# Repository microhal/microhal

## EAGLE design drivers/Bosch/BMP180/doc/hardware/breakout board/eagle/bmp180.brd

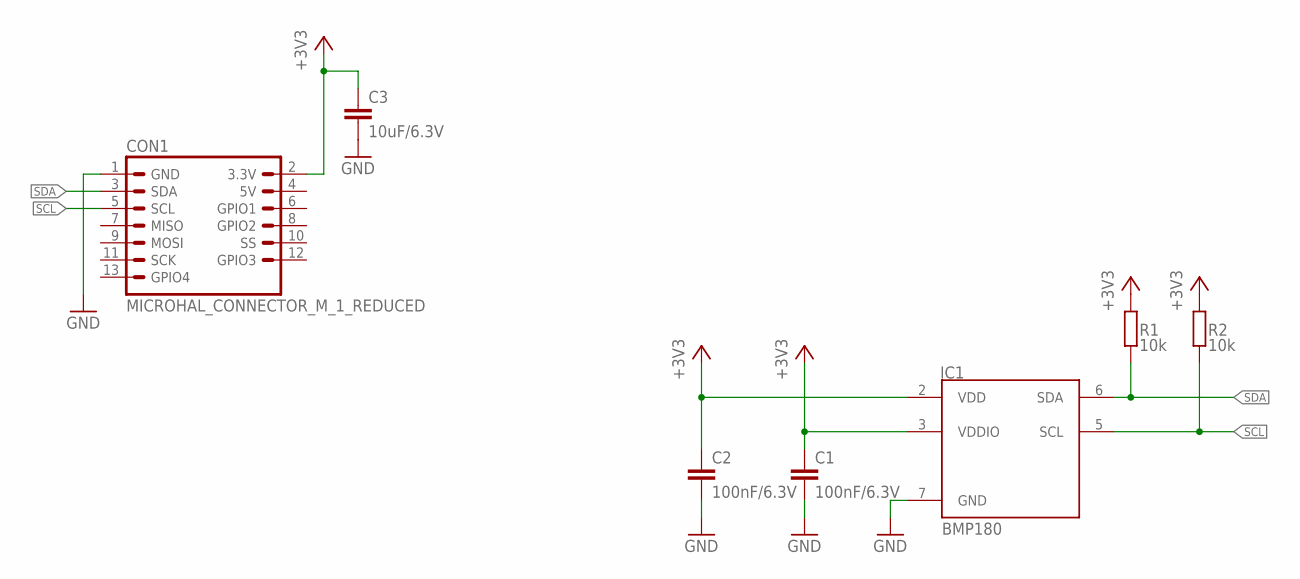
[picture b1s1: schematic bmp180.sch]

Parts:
C1, C2: 100nF/6.3V; C0603K
C3: 10uF/6.3V; C0805K
CON1: MICROHAL_CONNECTOR_M_1_REDUCED; MICROHAL_CONNECTOR_M_1_REDUCED_EDGE
IC1: BMP180; LGA7
R1, R2: 10k; R0603

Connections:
+3V3: C1.1, C2.1, C3.1, CON1.2 (3.3V), IC1.2 (VDD), IC1.3 (VDDIO), R1.2, R2.2
GND: C1.2, C2.2, C3.2, CON1.1 (GND), IC1.7 (GND)
SCL: CON1.5 (SCL), IC1.5 (SCL), R2.1
SDA: CON1.3 (SDA), IC1.6 (SDA), R1.1

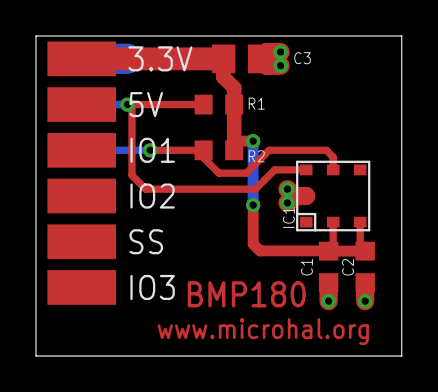
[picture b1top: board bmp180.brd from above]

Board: 2 copper layers, 20.3 x 17.8 mm, 7 parts (0 on the bottom side), 4 nets.

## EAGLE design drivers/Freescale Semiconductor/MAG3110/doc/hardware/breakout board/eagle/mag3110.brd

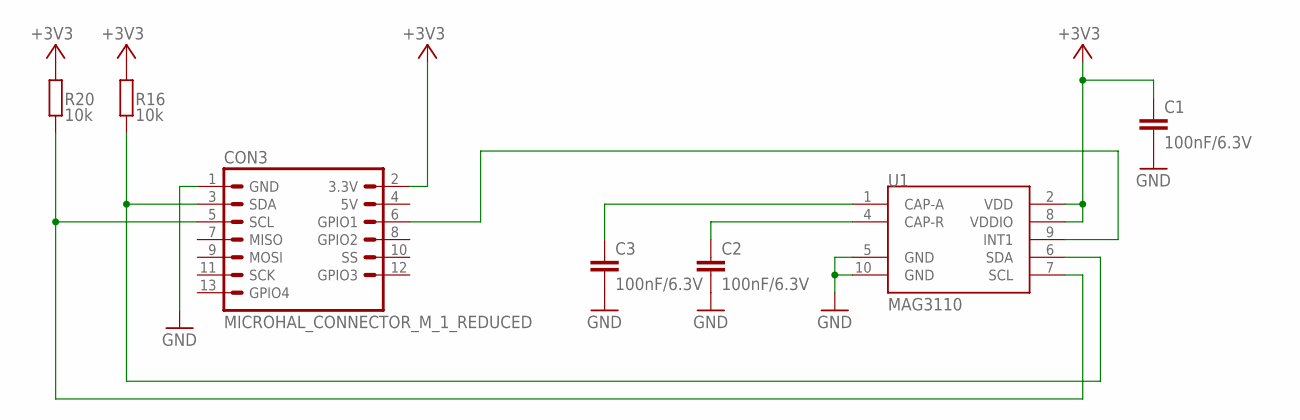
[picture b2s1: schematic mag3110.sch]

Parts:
C1, C2, C3: 100nF/6.3V; C0603K
CON3: MICROHAL_CONNECTOR_M_1_REDUCED; MICROHAL_CONNECTOR_M_1_REDUCED_EDGE
R16, R20: 10k; R0603
U1: MAG3110; DFN-10

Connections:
+3V3: C1.1, CON3.2 (3.3V), R16.2, R20.2, U1.2 (VDD), U1.8 (VDDIO)
GND: C1.2, C2.2, C3.2, CON3.1 (GND), U1.5 (GND), U1.10 (GND)
unnamed: C2.1, U1.4 (CAP-R)
unnamed: CON3.3 (SDA), R16.1, U1.6 (SDA)
unnamed: CON3.5 (SCL), R20.1, U1.7 (SCL)
unnamed: CON3.6 (GPIO1), U1.9 (INT1)
unnamed: C3.1, U1.1 (CAP-A)

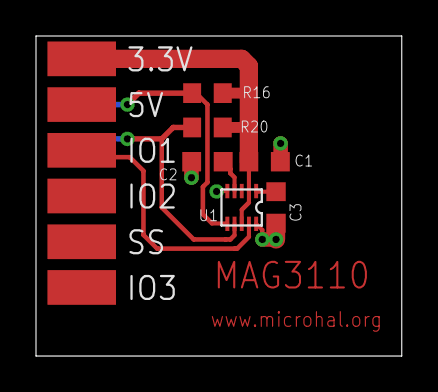
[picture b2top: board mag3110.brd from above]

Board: 2 copper layers, 20.3 x 17.8 mm, 7 parts (0 on the bottom side), 7 nets.

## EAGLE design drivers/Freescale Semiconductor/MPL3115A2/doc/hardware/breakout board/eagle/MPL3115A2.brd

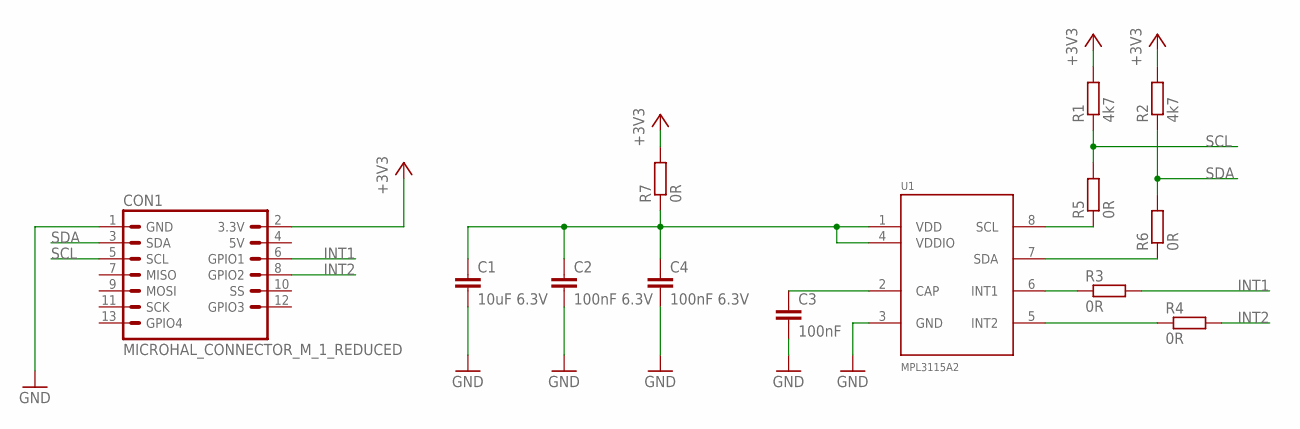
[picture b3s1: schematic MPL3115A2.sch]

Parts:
C1: 10uF 6.3V; C0603K
C2, C4: 100nF 6.3V; C0603K
C3: 100nF; C0603K
CON1: MICROHAL_CONNECTOR_M_1_REDUCED; MICROHAL_CONNECTOR_M_1_REDUCED_EDGE
R1, R2: 4k7; R0603
R3, R4, R5, R6, R7: 0R; R0603
U1: MPL3115A2

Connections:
+3V3: CON1.2 (3.3V), R1.2, R2.2, R7.2
GND: C1.2, C2.2, C3.2, C4.2, CON1.1 (GND), U1.3 (GND)
INT1: CON1.6 (GPIO1), R3.2
INT2: CON1.8 (GPIO2), R4.2
unnamed: R5.1, U1.8 (SCL)
unnamed: R6.1, U1.7 (SDA)
unnamed: C1.1, C2.1, C4.1, R7.1, U1.1 (VDD), U1.4 (VDDIO)
unnamed: C3.1, U1.2 (CAP)
unnamed: R3.1, U1.6 (INT1)
unnamed: R4.1, U1.5 (INT2)
SCL: CON1.5 (SCL), R1.1, R5.2
SDA: CON1.3 (SDA), R2.1, R6.2

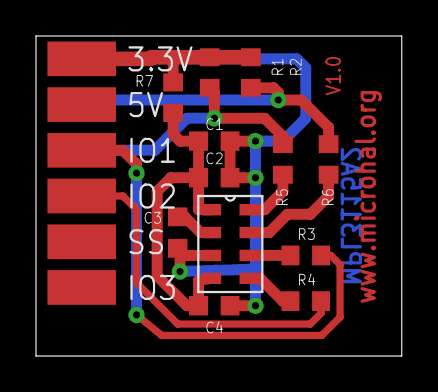
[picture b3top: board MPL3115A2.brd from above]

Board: 2 copper layers, 20.3 x 17.8 mm, 13 parts (0 on the bottom side), 12 nets.

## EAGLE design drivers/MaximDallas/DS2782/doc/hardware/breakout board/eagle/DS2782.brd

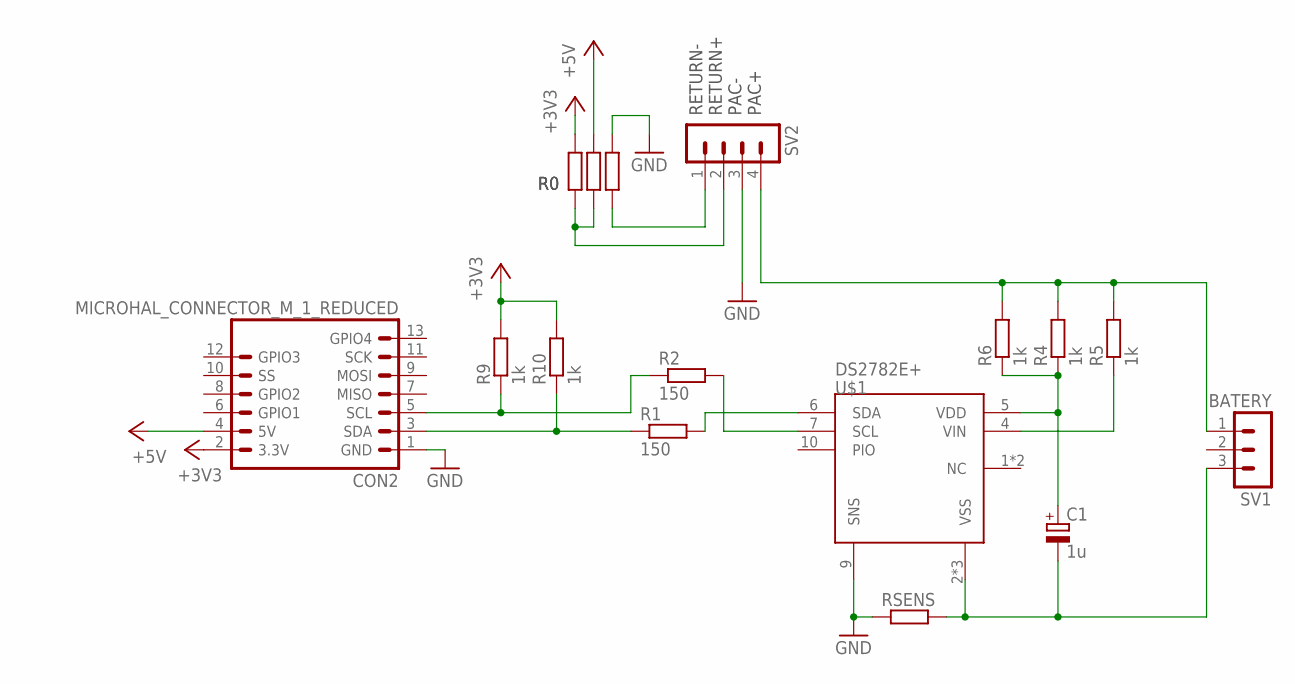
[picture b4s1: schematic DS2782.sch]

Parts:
C1: 1u; 153CLV-0405
CON2: MICROHAL_CONNECTOR_M_1_REDUCED; MICROHAL_CONNECTOR_M_1_REDUCED_EDGE
R1, R2: 150; R0603
R3, R7, R8: R-EU_R0603; R0603
R4, R5, R6, R9, R10: 1k; R0603
RSENS: R-EU_R1206; R1206
SV1: BATERY; MA03-1
SV2: MA04-1
U$1: DS2782E+; TDFN-10

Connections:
+3V3: CON2.2 (3.3V), R8.2, R9.2, R10.2
+5V: CON2.4 (5V), R7.2
GND: CON2.1 (GND), R3.2, RSENS.1, SV2.3, U$1.9 (SNS)
unnamed: R1.2, U$1.6 (SDA)
unnamed: R2.2, U$1.7 (SCL)
unnamed: CON2.3 (SDA), R1.1, R10.1
unnamed: C1.+, R4.1, R6.1, U$1.5 (VDD)
unnamed: R5.1, U$1.4 (VIN)
unnamed: C1.-, RSENS.2, SV1.3, U$1.2 (VSS), U$1.3 (VSS), U$1.PAD1 (VSS)
unnamed: R4.2, R5.2, R6.2, SV1.1, SV2.4
unnamed: R7.1, R8.1, SV2.2
unnamed: CON2.5 (SCL), R2.1, R9.1
unnamed: R3.1, SV2.1

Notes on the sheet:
RETURN- RETURN+ PAC- PAC+

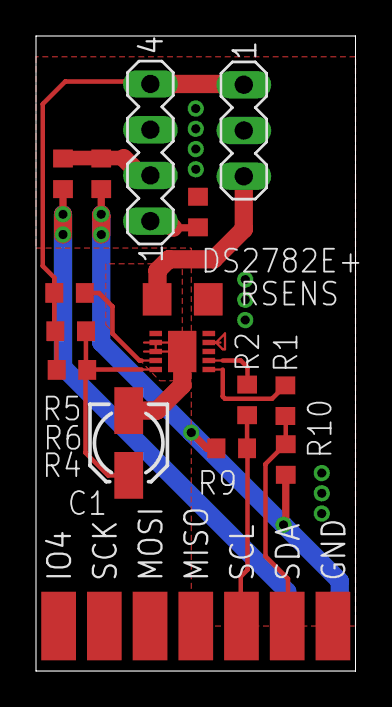
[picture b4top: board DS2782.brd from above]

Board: 2 copper layers, 17.8 x 35.3 mm, 16 parts (1 on the bottom side), 13 nets.

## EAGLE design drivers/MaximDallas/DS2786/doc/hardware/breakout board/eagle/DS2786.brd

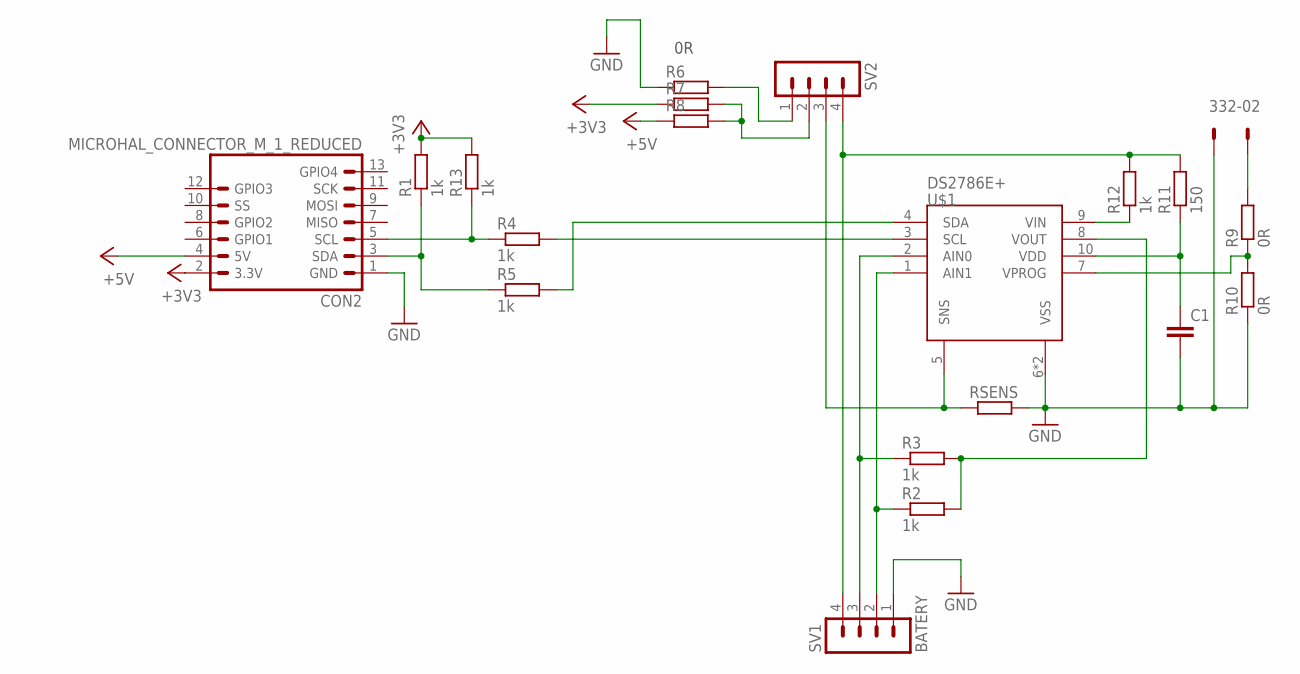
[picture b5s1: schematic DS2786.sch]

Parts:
C1: C-EUC0603; C0603
CON2: MICROHAL_CONNECTOR_M_1_REDUCED; MICROHAL_CONNECTOR_M_1_REDUCED_EDGE
R1, R2, R3, R4, R5, R12, R13: 1k; R0603
R6, R7, R8: R-EU_R0603; R0603
R9, R10: 0R; R0603
R11: 150; R0603
RSENS: R-EU_R1206; R1206
SV1: BATERY; MA04-1
SV2: MA04-1
U$1: DS2786E+; TDFN-10
X1: 332-02

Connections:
+3V3: CON2.2 (3.3V), R1.2, R7.1, R13.2
+5V: CON2.4 (5V), R8.1
GND: C1.2, CON2.1 (GND), R6.1, R10.1, RSENS.2, SV1.1, U$1.6 (VSS), U$1.PAD1 (VSS), X1.1
unnamed: R9.2, X1.2
unnamed: R2.2, R3.2, U$1.8 (VOUT)
unnamed: RSENS.1, SV2.3, U$1.5 (SNS)
unnamed: CON2.5 (SCL), R4.1, R13.1
unnamed: CON2.3 (SDA), R1.1, R5.1
unnamed: R4.2, U$1.3 (SCL)
unnamed: R5.2, U$1.4 (SDA)
unnamed: R11.2, R12.2, SV1.4, SV2.4
unnamed: R6.2, SV2.1
unnamed: R7.2, R8.2, SV2.2
unnamed: C1.1, R11.1, U$1.10 (VDD)
unnamed: R9.1, R10.2, U$1.7 (VPROG)
unnamed: R12.1, U$1.9 (VIN)
unnamed: R2.1, SV1.2, U$1.1 (AIN1)
unnamed: R3.1, SV1.3, U$1.2 (AIN0)

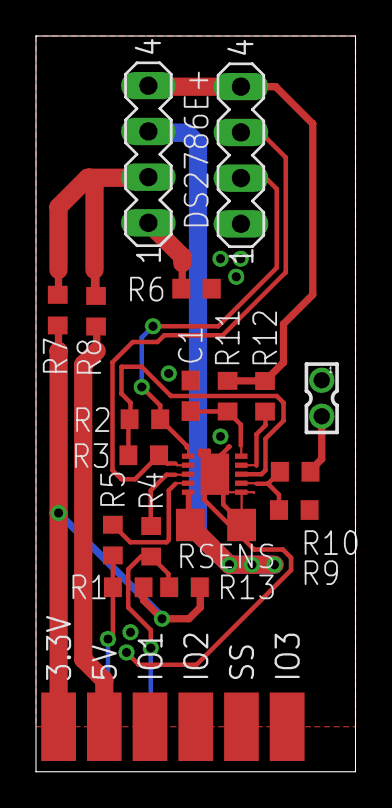
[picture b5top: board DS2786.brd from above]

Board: 2 copper layers, 17.8 x 40.9 mm, 20 parts (0 on the bottom side), 18 nets.

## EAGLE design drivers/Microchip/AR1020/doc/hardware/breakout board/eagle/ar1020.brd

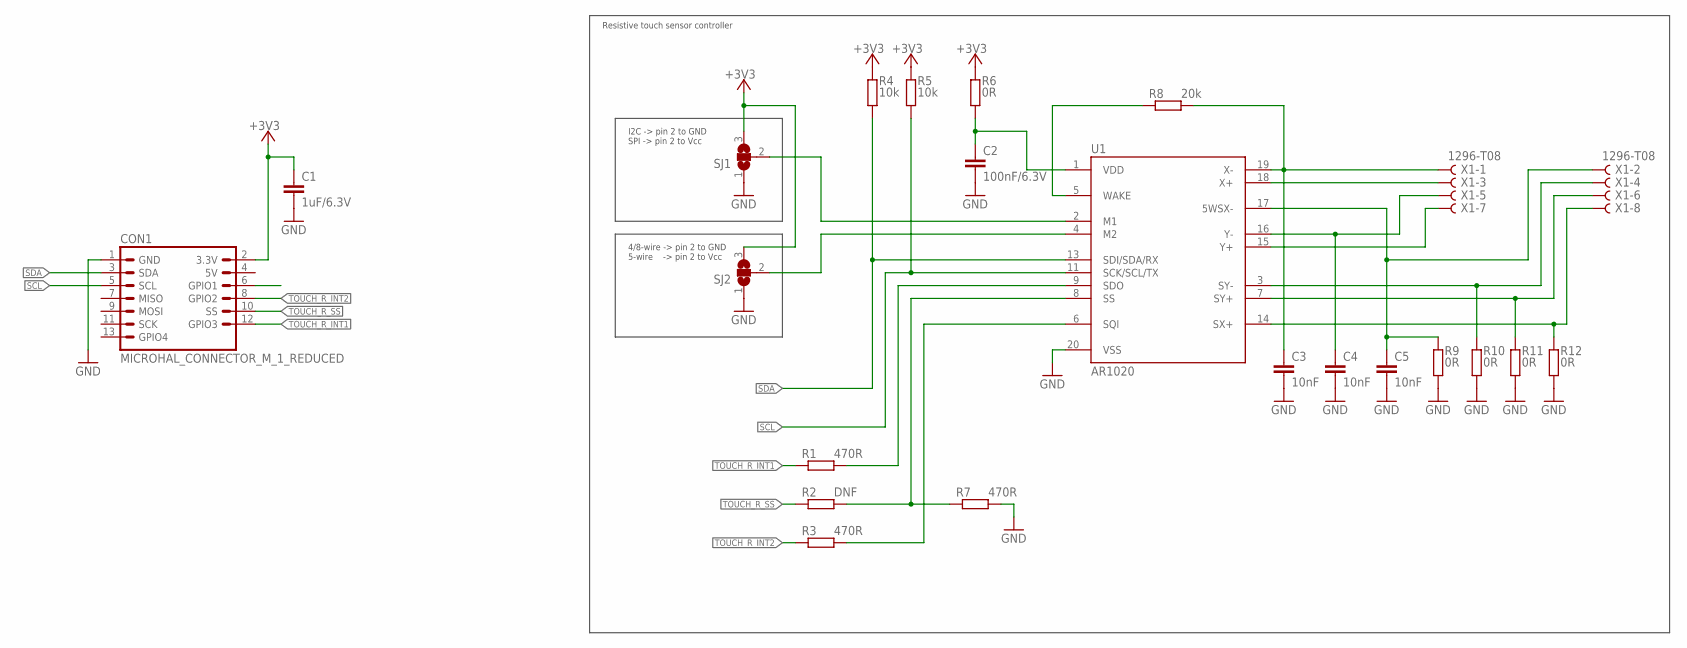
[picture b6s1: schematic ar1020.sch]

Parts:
C1: 1uF/6.3V; C0603K
C2: 100nF/6.3V; C0603K
C3, C4, C5: 10nF; C0603K
CON1: MICROHAL_CONNECTOR_M_1_REDUCED; MICROHAL_CONNECTOR_M_1_REDUCED_EDGE
R1, R3, R7: 470R; R0603
R2: DNF; R0603
R4, R5: 10k; R0603
R6, R9, R10, R11, R12: 0R; R0603
R8: 20k; R0603
SJ1, SJ2: SJ2W; SJ_2
U1: AR1020; SSOP20
X1: 1296-T08; 1296-08

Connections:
+3V3: C1.1, CON1.2 (3.3V), R4.1, R5.1, R6.1, SJ1.3, SJ2.3
GND: C1.2, C2.2, C3.2, C4.2, C5.2, CON1.1 (GND), R7.1, R9.2, R10.2, R11.2, R12.2, SJ1.1, SJ2.1, U1.20 (VSS)
unnamed: SJ1.2, U1.2 (M1)
unnamed: SJ2.2, U1.4 (M2)
unnamed: C2.1, R6.2, U1.1 (VDD)
unnamed: R8.2, U1.5 (WAKE)
unnamed: C3.1, R8.1, U1.19 (X-), X1.1
unnamed: C4.1, U1.16 (Y-), X1.5
unnamed: C5.1, R9.1, U1.17 (5WSX-), X1.2
unnamed: U1.18 (X+), X1.3
unnamed: U1.15 (Y+), X1.7
unnamed: R10.1, U1.3 (SY-), X1.4
unnamed: R11.1, U1.7 (SY+), X1.6
unnamed: R12.1, U1.14 (SX+), X1.8
unnamed: R1.1, U1.9 (SDO)
unnamed: R2.1, R7.2, U1.8 (SS)
unnamed: R3.1, U1.6 (SQI)
SCL: CON1.5 (SCL), R5.2, U1.11 (SCK/SCL/TX)
SDA: CON1.3 (SDA), R4.2, U1.13 (SDI/SDA/RX)
TOUCH_R_INT1: CON1.12 (GPIO3), R1.2
TOUCH_R_INT2: CON1.8 (GPIO2), R3.2
TOUCH_R_SS: CON1.10 (SS), R2.2

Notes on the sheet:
4/8-wire -> pin 2 to GND 5-wire -> pin 2 to Vcc
I2C -> pin 2 to GND SPI -> pin 2 to Vcc
Resistive touch sensor controller

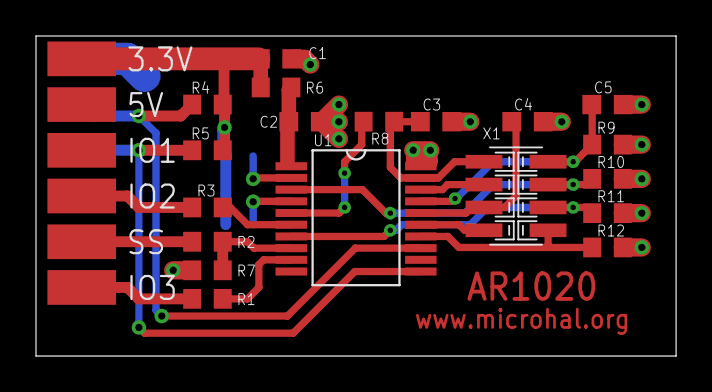
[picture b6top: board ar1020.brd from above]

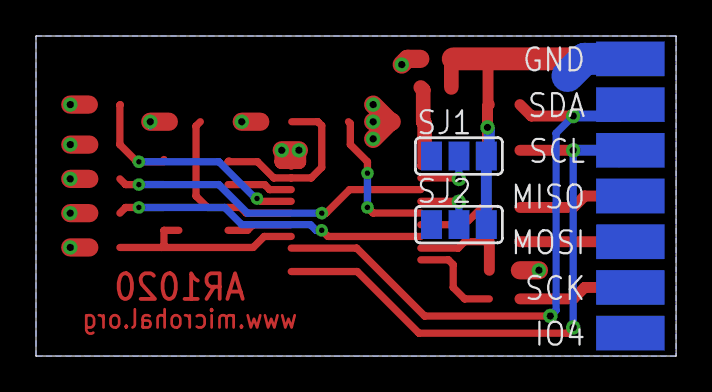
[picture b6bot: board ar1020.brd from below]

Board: 2 copper layers, 35.6 x 17.8 mm, 22 parts (2 on the bottom side), 22 nets.

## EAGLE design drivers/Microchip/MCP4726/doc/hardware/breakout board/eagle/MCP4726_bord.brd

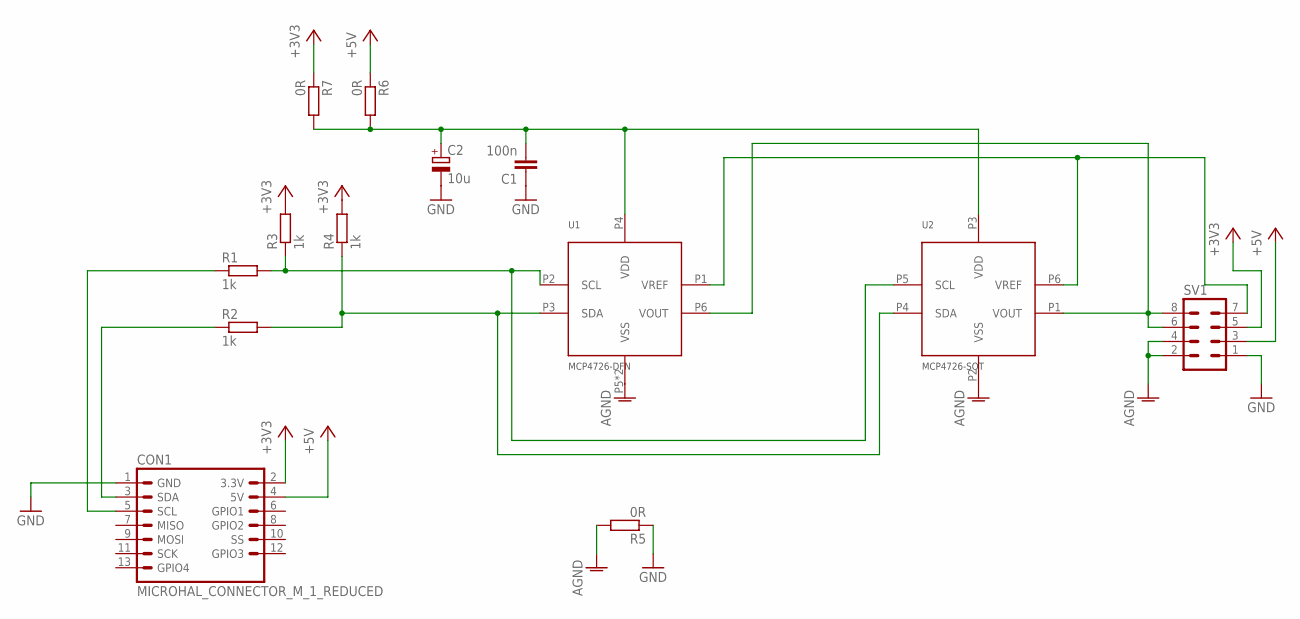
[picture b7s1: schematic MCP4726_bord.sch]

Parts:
C1: 100n; C0603
C2: 10u; 140CLH-0810
CON1: MICROHAL_CONNECTOR_M_1_REDUCED; MICROHAL_CONNECTOR_M_1_REDUCED_EDGE
R1, R2, R3, R4: 1k; R0603
R5, R6, R7: 0R; R0603
SV1: MA04-2
U1: MCP4726-DFN; DFN-6
U2: MCP4726-SOT; SOT-23-6

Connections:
+3V3: CON1.2 (3.3V), R3.2, R4.2, R7.1, SV1.5
+5V: CON1.4 (5V), R6.1, SV1.3
AGND: R5.2, SV1.2, SV1.4, U1.P5 (VSS), U1.PAD (VSS), U2.P2 (VSS)
GND: C1.1, C2.-, CON1.1 (GND), R5.1, SV1.1
unnamed: CON1.3 (SDA), R2.1
unnamed: R2.2, R4.1, U1.P3 (SDA), U2.P4 (SDA)
unnamed: CON1.5 (SCL), R1.1
unnamed: R1.2, R3.1, U1.P2 (SCL), U2.P5 (SCL)
unnamed: SV1.6, SV1.8, U1.P6 (VOUT), U2.P1 (VOUT)
unnamed: C1.2, C2.+, R6.2, R7.2, U1.P4 (VDD), U2.P3 (VDD)
unnamed: SV1.7, U1.P1 (VREF), U2.P6 (VREF)

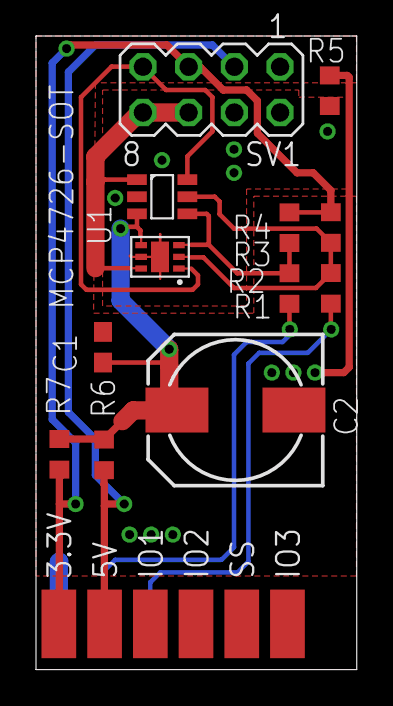
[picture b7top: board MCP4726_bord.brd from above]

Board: 2 copper layers, 17.8 x 35.2 mm, 13 parts (0 on the bottom side), 11 nets.

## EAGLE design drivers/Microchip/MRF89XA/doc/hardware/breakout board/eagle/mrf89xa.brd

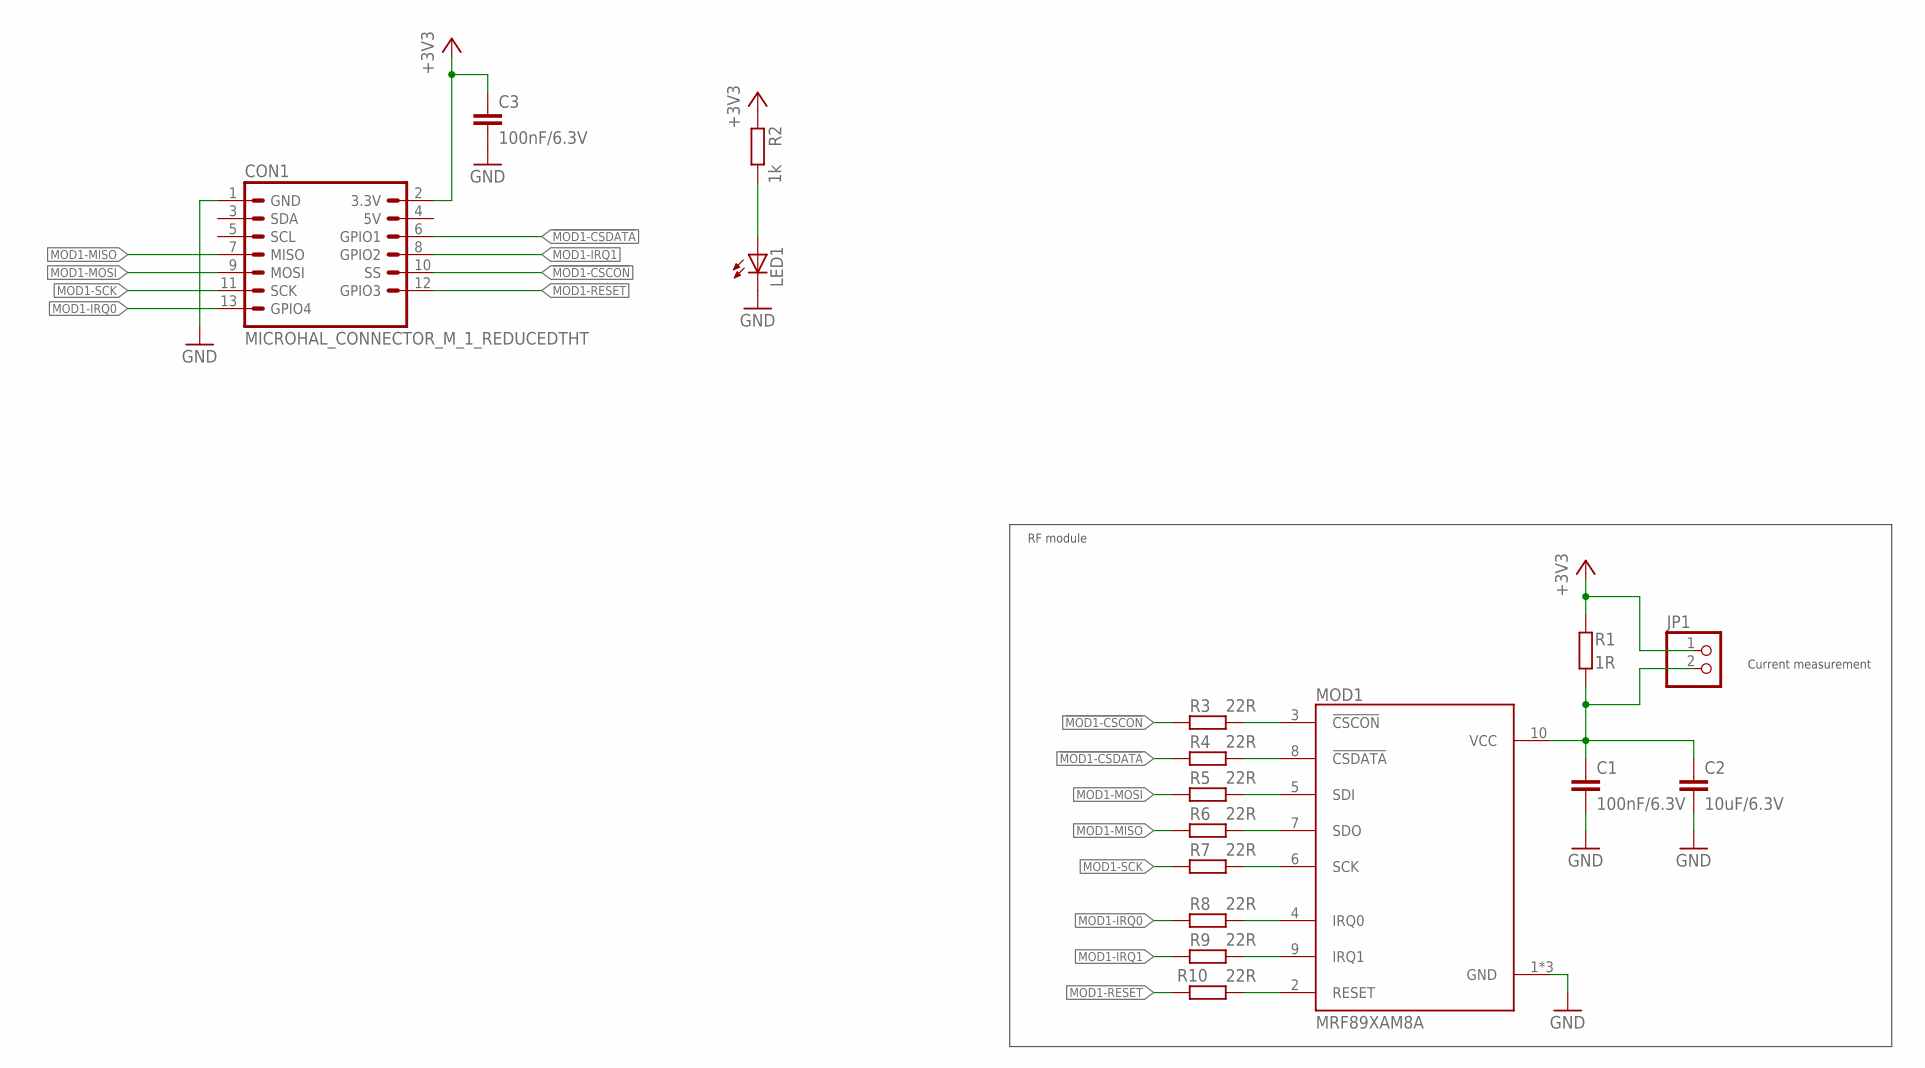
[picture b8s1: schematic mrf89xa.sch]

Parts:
C1, C3: 100nF/6.3V; C0603K
C2: 10uF/6.3V; C1206K
CON1: MICROHAL_CONNECTOR_M_1_REDUCEDTHT; MA07-2
JP1: PINHD-1X2; 1X02
LED1: LEDCHIP-LED0603; CHIP-LED0603
MOD1: MRF89XAM8A
R1: 1R; R0603
R2: 1k; R0603
R3, R4, R5, R6, R7, R8, R9, R10: 22R; R0603

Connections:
!MOD1-CSCON: CON1.10 (SS), R3.2
!MOD1-CSDATA: CON1.6 (GPIO1), R4.2
+3V3: C3.1, CON1.2 (3.3V), JP1.1, R1.2, R2.2
GND: C1.2, C2.2, C3.2, CON1.1 (GND), LED1.C, MOD1.1 (GND), MOD1.11 (GND), MOD1.12 (GND)
MOD1-IRQ0: CON1.13 (GPIO4), R8.2
MOD1-IRQ1: CON1.8 (GPIO2), R9.2
MOD1-MISO: CON1.7 (MISO), R6.2
MOD1-MOSI: CON1.9 (MOSI), R5.2
MOD1-RESET: CON1.12 (GPIO3), R10.2
MOD1-SCK: CON1.11 (SCK), R7.2
unnamed: C1.1, C2.1, JP1.2, MOD1.10 (VCC), R1.1
unnamed: LED1.A, R2.1
unnamed: MOD1.3 (!CSCON), R3.1
unnamed: MOD1.8 (!CSDATA), R4.1
unnamed: MOD1.5 (SDI), R5.1
unnamed: MOD1.7 (SDO), R6.1
unnamed: MOD1.6 (SCK), R7.1
unnamed: MOD1.4 (IRQ0), R8.1
unnamed: MOD1.9 (IRQ1), R9.1
unnamed: MOD1.2 (RESET), R10.1

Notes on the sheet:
RF module
Current measurement

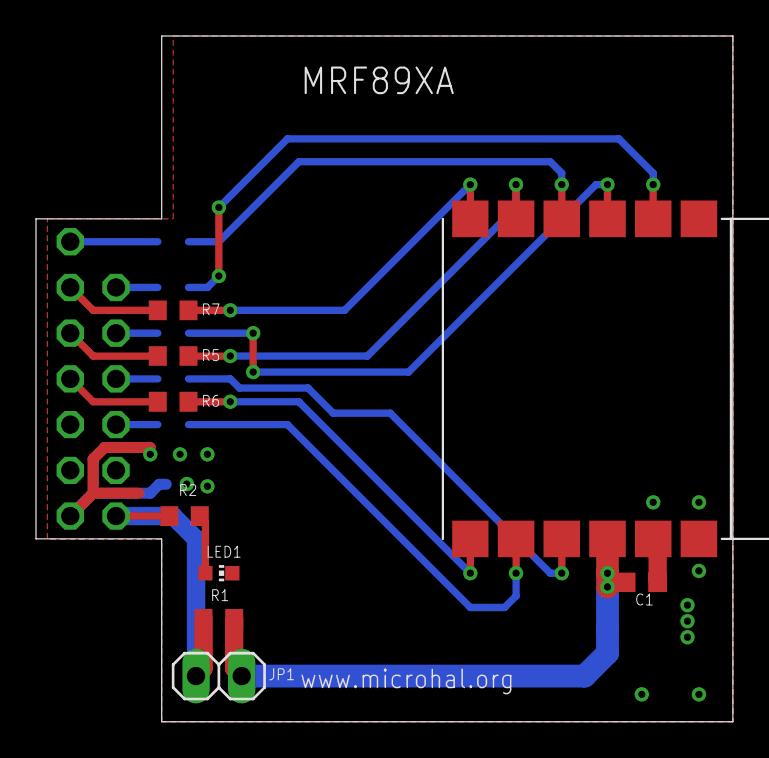
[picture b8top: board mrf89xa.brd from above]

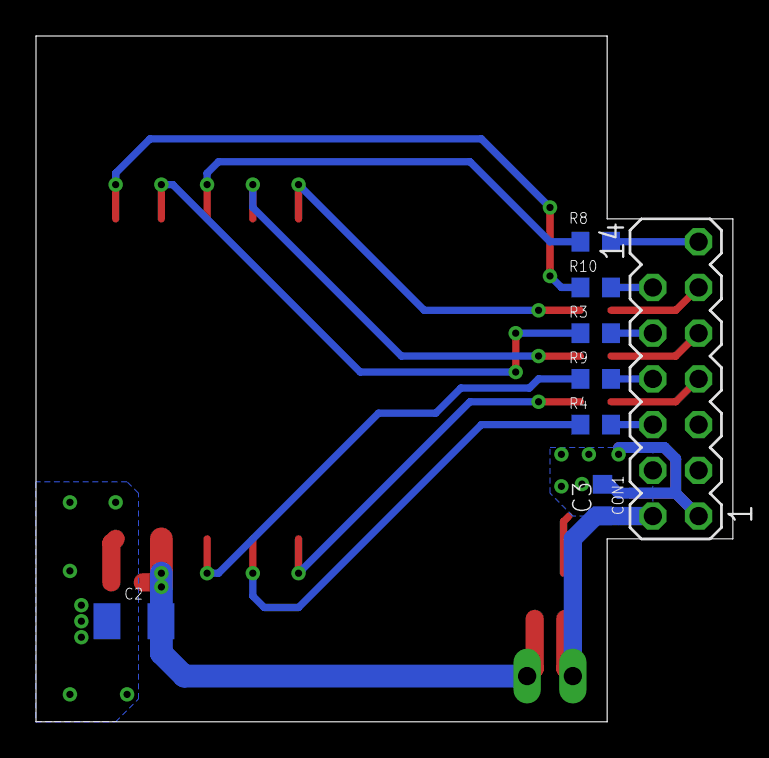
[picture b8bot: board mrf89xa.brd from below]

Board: 2 copper layers, 38.7 x 38.1 mm, 17 parts (8 on the bottom side), 20 nets.

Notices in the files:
parts and their libraries:
bmp180: Copyright (c) 2016, microHAL
All rights reserved.
